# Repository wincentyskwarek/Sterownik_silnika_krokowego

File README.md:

# Sterownik_silnika_krokowego
Jakiś czas temu projektowałem sterownik silnika krokowego dwufazowego opartego na mikrokontrolerze Atmega328PU o następującej funkcjonalności:
1. Regulacja prędkości obrotowej za pomocą impulsatora od kilku do kilkuset kroków na sekundę. 
2. Możliwość zapisu ustawień prędkości po wciśnięciu przycisku impulsatora.
3. Obroty prawe-lewe zmieniane przełącznikiem.
4. Start-Stop zmieniane przełącznikiem.
5. Szybkie obroty po naciśnięciu przycisku.
6. Wyświetlacz.
7. Zasilanie z zasilacza DC 5-35 V z regulacją napięcia wyjściowego na silniki (oczywiście potrzebny sterownik np. TB6600).

Mam do odsprzedania kilka takich kompletnych sterowników, które mi zostały oraz kilka płytek drukowanych zaprojektowanych przeze mnie i wykonanych w profesjonalnym zakładzie. Rozmiar płytki (92 x 55)mm
W wolnej chwili postaram się dodać obszerniejszą dokumentację

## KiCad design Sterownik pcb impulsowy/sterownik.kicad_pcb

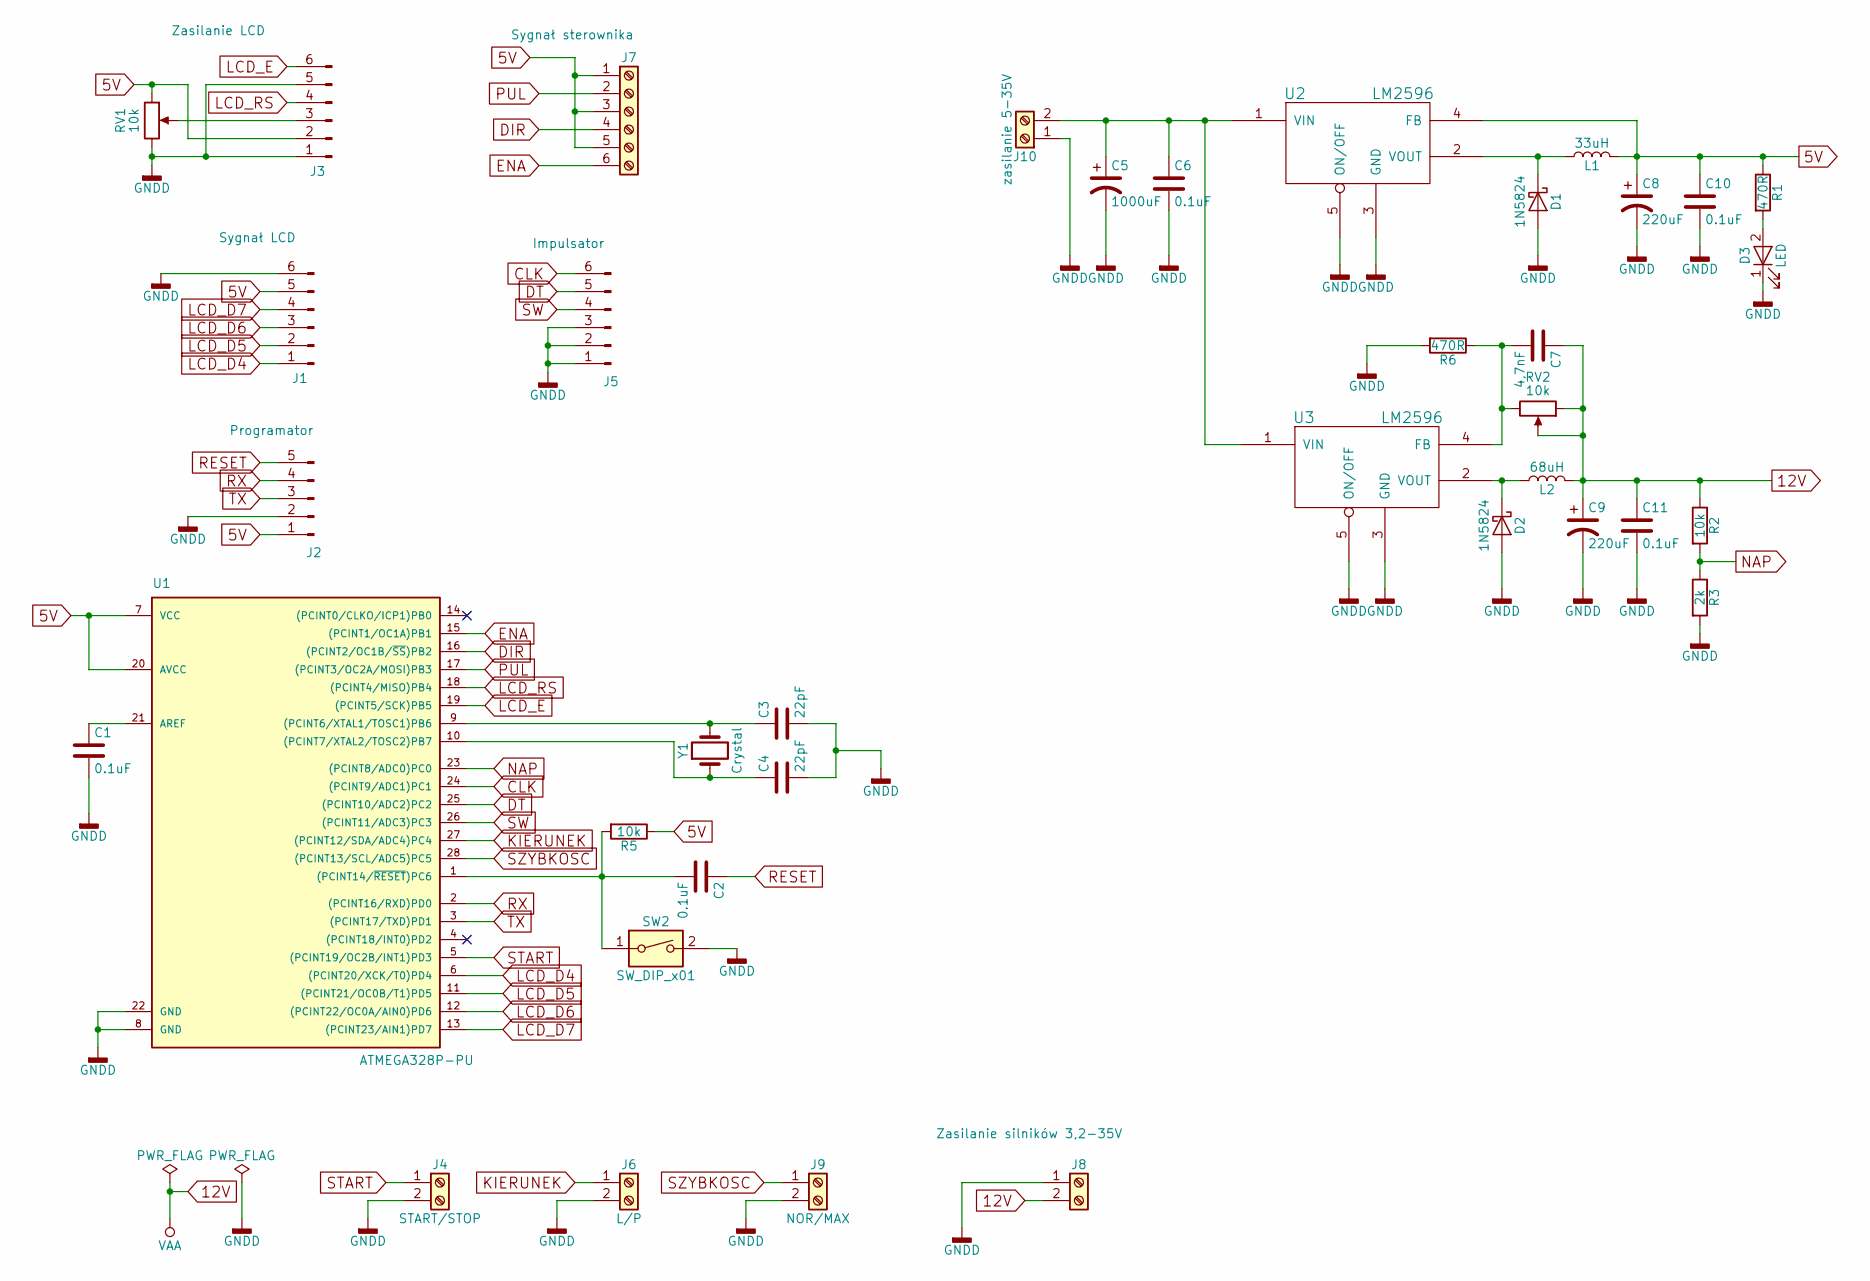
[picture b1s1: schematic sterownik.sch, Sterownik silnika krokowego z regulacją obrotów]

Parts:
C1, C2, C6, C10, C11: 0.1uF; C_Disc_D3.8mm_W2.6mm_P2.50mm
C3, C4: 22pF; C_Disc_D3.8mm_W2.6mm_P2.50mm
C5: 1000uF; CP_Radial_D13.0mm_P5.00mm
C7: 4,7nF; C_Disc_D3.8mm_W2.6mm_P2.50mm
C8, C9: 220uF; CP_Radial_D5.0mm_P2.00mm
D1: 1N5824; D_DO-27_P15.24mm_Horizontal
D2: 1N5824; D_DO-27_P12.70mm_Horizontal
D3: LED; LED_D3.0mm
J1: Sygnał LCD; JST_XH_B06B-XH-A_06x2.50mm_Straight
J2: Programator; Pin_Header_Straight_1x05_Pitch2.54mm
J3: Zasilanie LCD; JST_XH_B06B-XH-A_06x2.50mm_Straight
J4: START/STOP; JST_XH_B02B-XH-A_02x2.50mm_Straight
J5: Impulsator; JST_XH_B06B-XH-A_06x2.50mm_Straight
J6: L/P; JST_XH_B02B-XH-A_02x2.50mm_Straight
J7: Sygnał sterownika; TerminalBlock_bornier-6_P5.08mm
J8: Zasilanie silników 3,2-35V; TerminalBlock_bornier-2_P5.08mm
J9: NOR/MAX; JST_XH_B02B-XH-A_02x2.50mm_Straight
J10: zasilanie 5-35V; TerminalBlock_bornier-2_P5.08mm
L1: 33uH; L_Toroid_Vertical_L19.1mm_W8.1mm_P7.10mm_Bourns_5700
L2: 68uH; L_Toroid_Vertical_L25.4mm_W14.7mm_P12.20mm_Vishay_TJ5_BigPa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
R1, R6: 470R; R_Axial_DIN0207_L6.3mm_D2.5mm_P10.16mm_Horizontal
R2, R5: 10k; R_Axial_DIN0207_L6.3mm_D2.5mm_P10.16mm_Horizontal
R3: 2k; R_Axial_DIN0207_L6.3mm_D2.5mm_P10.16mm_Horizontal
RV1: 10k; Potentiometer_Triwood_RM-065
RV2: 10k; Potentiometer_Trimmer_Bourns_3296W
SW2: SW_DIP_x01; SW_PUSH_6mm
U1: ATMEGA328P-PU; DIP-28_W7.62mm_LongPads
U2: LM2596; TO-220-5_Vertical_StaggeredType1
U3: LM2596; TO-220-5_Vertical_StaggeredType2
Y1: Crystal; Crystal_HC49-U_Vertical

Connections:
5V: C8.1, C10.1, J1.5, J2.1, J3.2, J7.1, J7.3, J7.5, L1.2, R1.1, R5.1, RV1.1, U1.7 (VCC), U1.20 (AVCC), U2.4 (FB)
12V: C7.1, C9.1, C11.1, J8.2, L2.2, R2.1, RV2.1, RV2.2
CLK: J5.6, U1.24 ((PCINT9/ADC1)PC1)
DIR: J7.4, U1.16 ((PCINT2/OC1B/~SS~)PB2)
DT: J5.5, U1.25 ((PCINT10/ADC2)PC2)
ENA: J7.6, U1.15 ((PCINT1/OC1A)PB1)
GNDD: C1.2, C3.2, C4.2, C5.2, C6.2, C8.2, C9.2, C10.2, C11.2, D1.2 (A), D2.2 (A), D3.1 (K), J1.6, J2.2, J3.1, J3.5, J4.2, J5.1, J5.2, J5.3, J6.2, J8.1, J9.2, J10.1, R3.2, R6.2, RV1.3, SW2.2, U1.8 (GND), U1.22 (GND), U2.3 (GND), U2.5 (ON/OFF), U3.3 (GND), U3.5 (ON/OFF)
KIERUNEK: J6.1, U1.27 ((PCINT12/SDA/ADC4)PC4)
LCD_D4: J1.1, U1.6 ((PCINT20/XCK/T0)PD4)
LCD_D5: J1.2, U1.11 ((PCINT21/OC0B/T1)PD5)
LCD_D6: J1.3, U1.12 ((PCINT22/OC0A/AIN0)PD6)
LCD_D7: J1.4, U1.13 ((PCINT23/AIN1)PD7)
LCD_E: J3.6, U1.19 ((PCINT5/SCK)PB5)
LCD_RS: J3.4, U1.18 ((PCINT4/MISO)PB4)
NAP: R2.2, R3.1, U1.23 ((PCINT8/ADC0)PC0)
unnamed: C1.1, U1.21 (AREF)
unnamed: C2.2, R5.2, SW2.1, U1.1 ((PCINT14/~RESET~)PC6)
unnamed: C3.1, U1.9 ((PCINT6/XTAL1/TOSC1)PB6), Y1.2
unnamed: C4.1, U1.10 ((PCINT7/XTAL2/TOSC2)PB7), Y1.1
unnamed: C5.1, C6.1, J10.2, U2.1 (VIN), U3.1 (VIN)
unnamed: C7.2, R6.1, RV2.3, U3.4 (FB)
unnamed: D1.1 (K), L1.1, U2.2 (VOUT)
unnamed: D2.1 (K), L2.1, U3.2 (VOUT)
unnamed: D3.2 (A), R1.2
unnamed: J3.3, RV1.2
PUL: J7.2, U1.17 ((PCINT3/OC2A/MOSI)PB3)
RESET: C2.1, J2.5
RX: J2.4, U1.2 ((PCINT16/RXD)PD0)
START: J4.1, U1.5 ((PCINT19/OC2B/INT1)PD3)
SW: J5.4, U1.26 ((PCINT11/ADC3)PC3)
SZYBKOSC: J9.1, U1.28 ((PCINT13/SCL/ADC5)PC5)
TX: J2.3, U1.3 ((PCINT17/TXD)PD1)

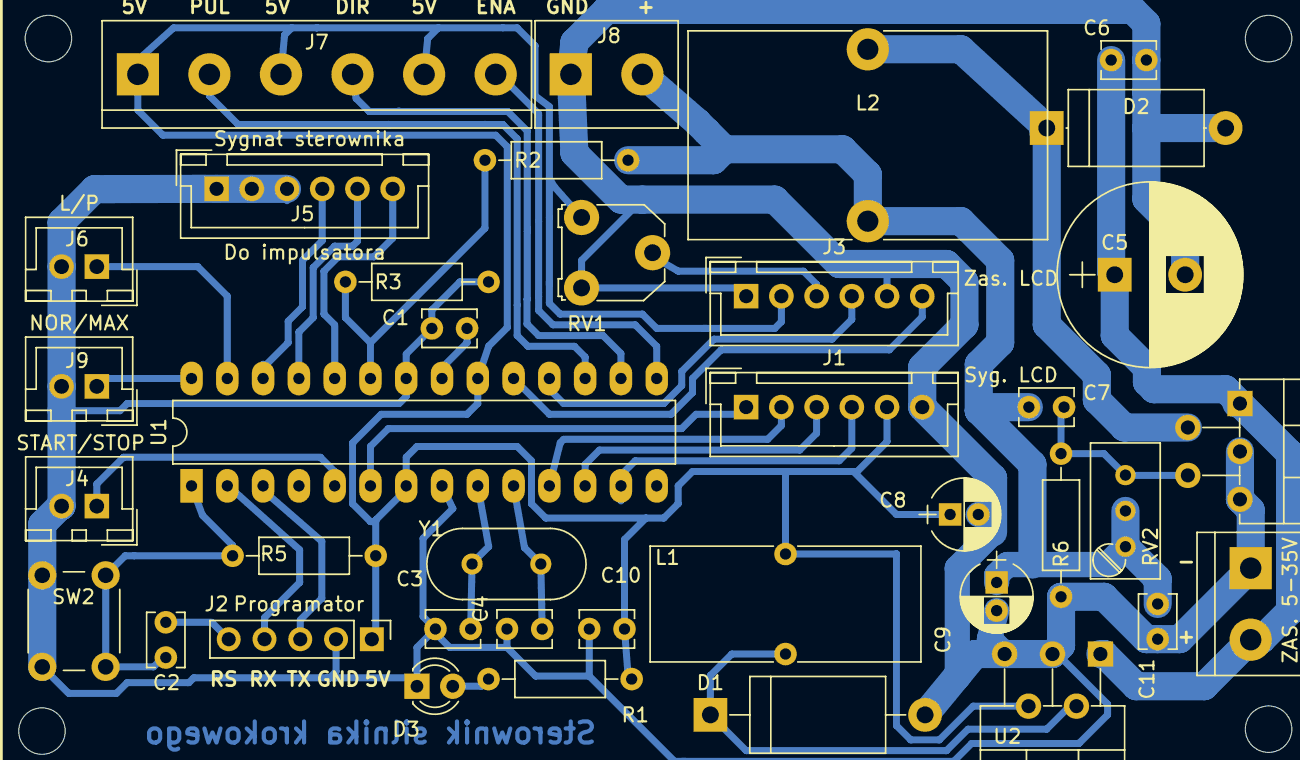
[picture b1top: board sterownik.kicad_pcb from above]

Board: 2 copper layers, 38 parts (0 on the bottom side), 32 nets.

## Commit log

2022-11-01 Pierwsza aktualizacja
